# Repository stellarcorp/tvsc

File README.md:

#TVSC

This repository is the principal codebase for the Tennessee Valley Stellar Corporation. We are a community-scale space agency in east Tennessee dedicated to the open development of technologies enabling the public use of space.

## Repository structure

There are three main sections to the repository. The most active development at the moment is taking place in the [hal](./hal) and the [electronics](./electronics) directories. The hal directory contains the Hardware Abstraction Layer. The electronics directory holds our PCB design work. The rest of the repository (the third section) consists of older code that is in need of maintenance/documentation or deletion.

## Getting started

### Bazel

We use Bazel for our build system. It is one of the few build tools that allow for multi-language, cross-platform hermetic builds. For more information, checkout https://bazel.build/

Part of Bazel is a command line tool called [Bazelisk](https://github.com/bazelbuild/bazelisk). This tool manages Bazel installations on your local machine and allows us to specify *in the repo itself* the version of Bazel to use and prevents build errors due to build system versioning. Bazelisk executables are checked into the top-level of this repo. Please use them when building.

On the first run of bazelisk on a given computer, it will download the correct version of Bazel. So, this first build may take a while.

### Toolchain

The build uses the local toolchain for desktop builds. This toolchain should support C++20.

For embedded builds, the toolchain and system libraries are downloaded from various external repositories.

The builds are designed to work on Linux. Other systems can be added as needed.

### Do a test build for your local system:

From the top-level of the repo,
```
./bazelisk-linux-amd64 build --config=nucleo_l452re //...
```

The first build will take a long time, but future builds should be relatively fast.

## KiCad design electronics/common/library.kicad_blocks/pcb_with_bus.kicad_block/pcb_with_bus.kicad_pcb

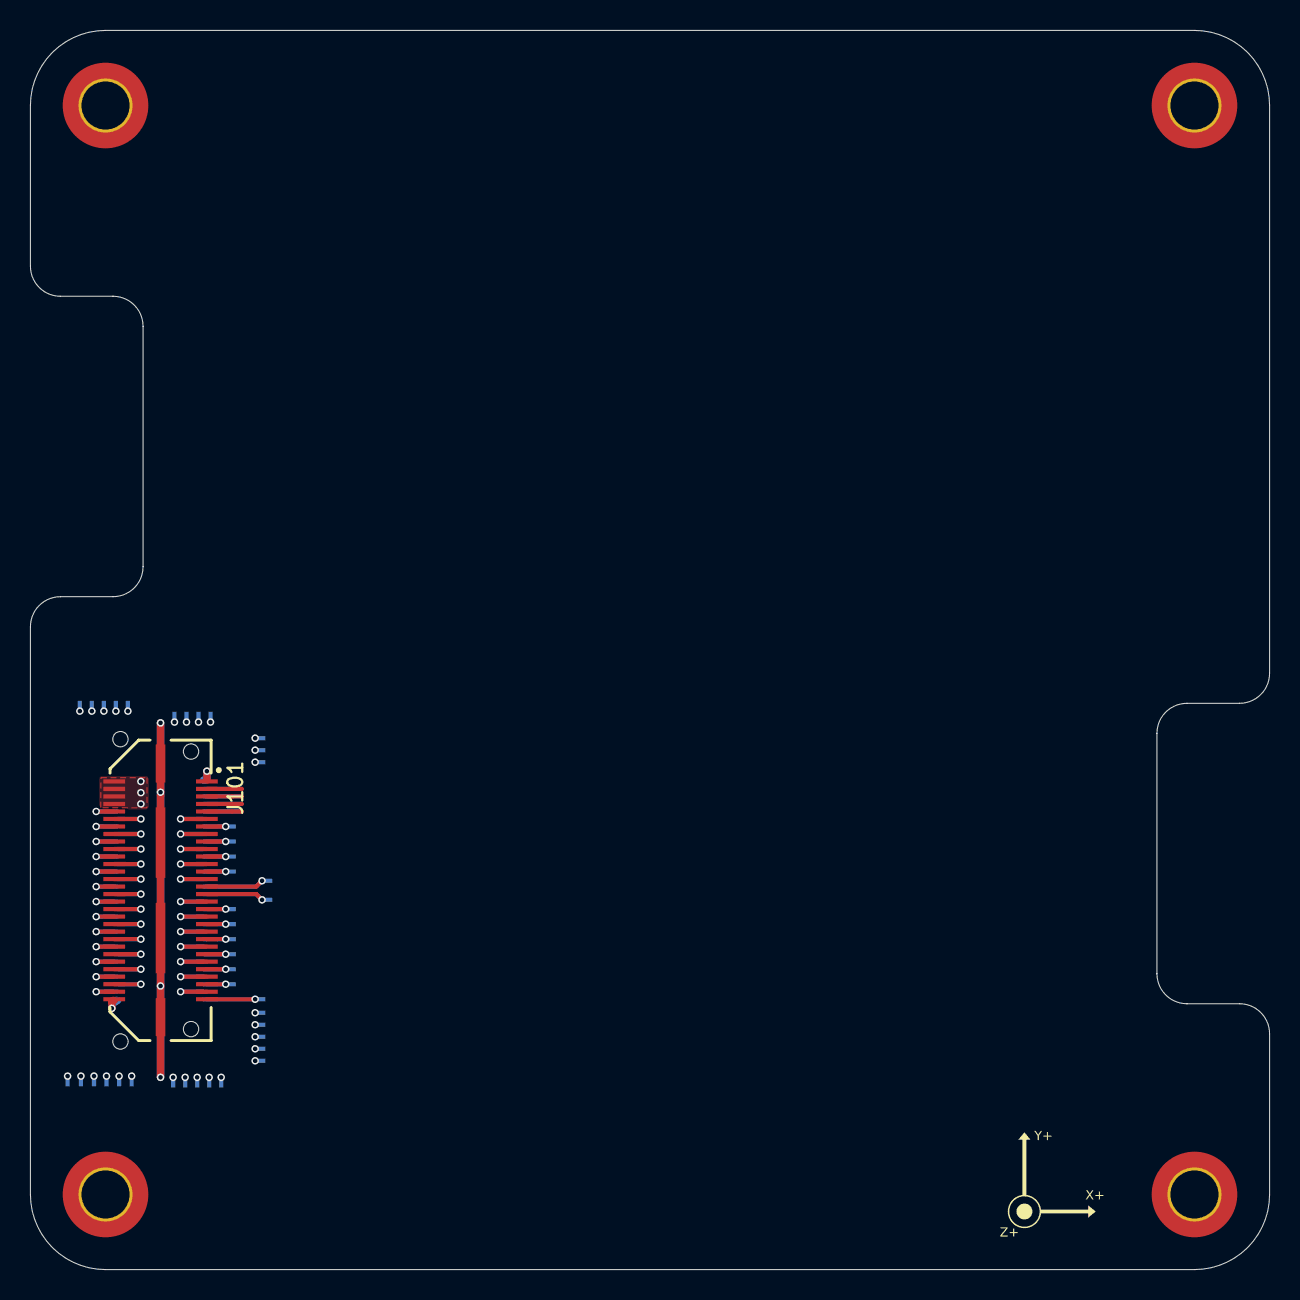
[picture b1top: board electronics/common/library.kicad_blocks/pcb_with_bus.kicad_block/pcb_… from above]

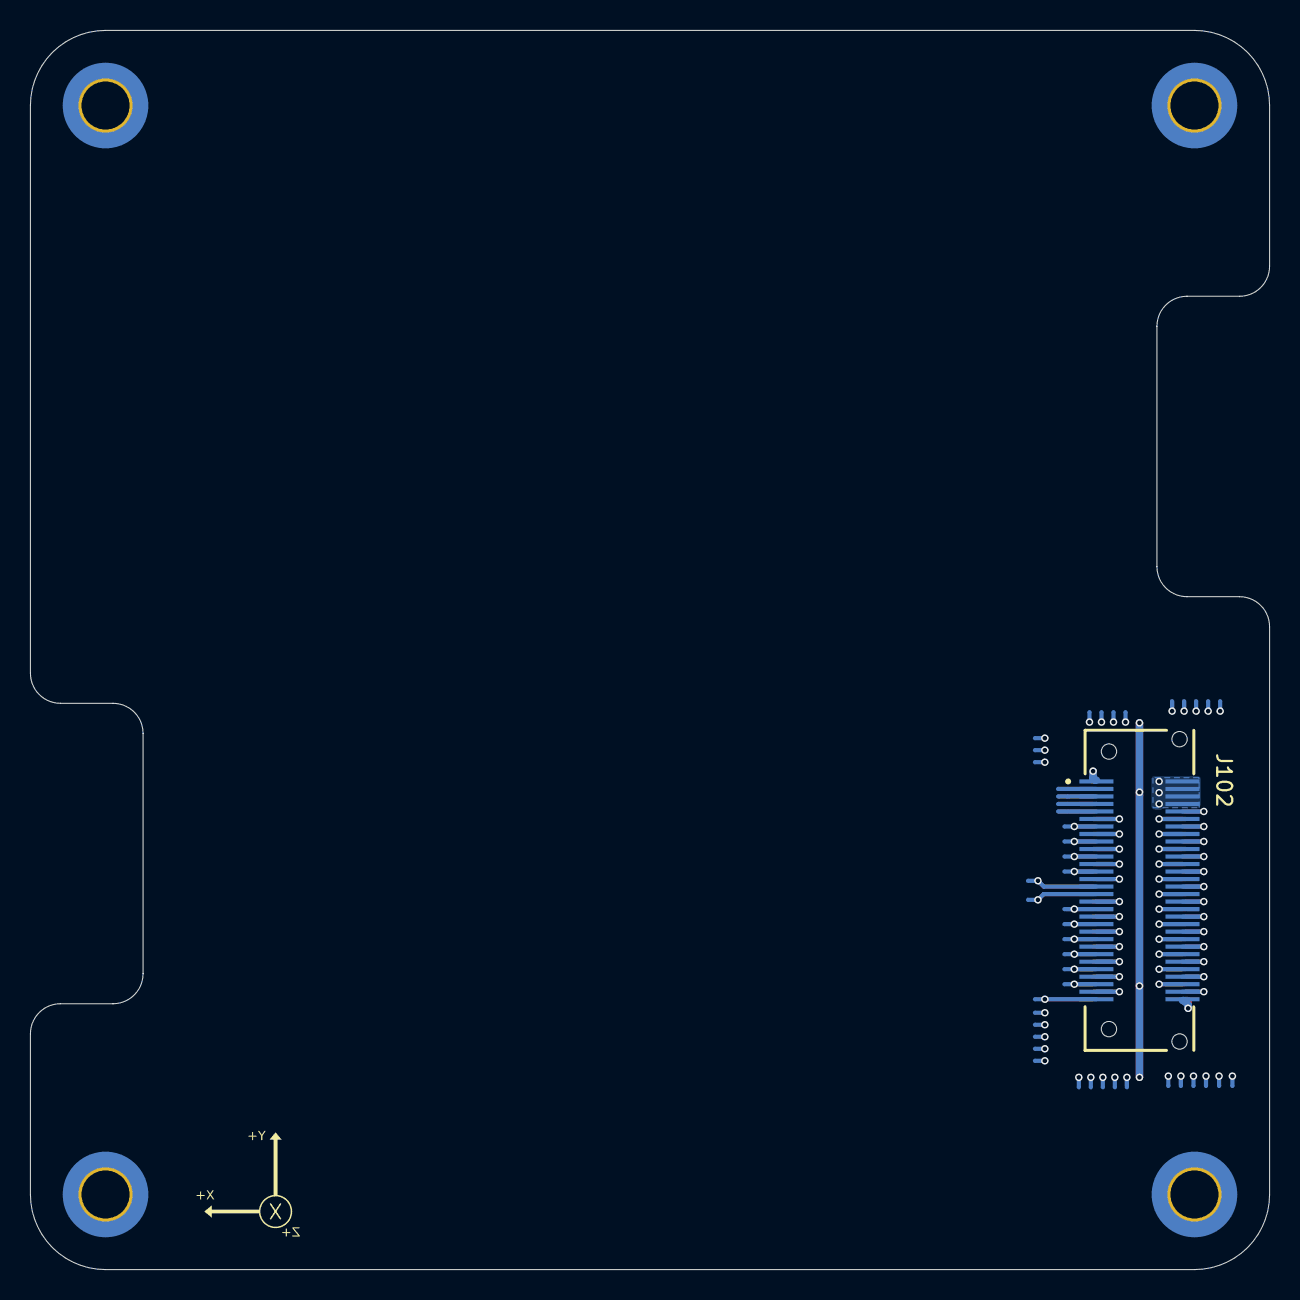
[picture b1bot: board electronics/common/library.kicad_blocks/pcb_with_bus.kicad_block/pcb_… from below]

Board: 4 copper layers, 82.5 x 82.5 mm, 52 parts (46 on the bottom side), 52 nets.

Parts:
J101: QTH-030-07-L-D-A; SAMTEC_QTH-030-07-L-D-A
J102: QSH-030-01-L-D-A; SAMTEC_QSH-030-01-L-D-A
NT101, NT102, NT103, NT104, NT105, NT106, NT107, NT108, NT109, NT110, NT111, NT112, NT113, NT114, NT115, NT116, NT117, NT118, NT119, NT120, NT121, NT122, NT123, NT124, NT125, NT126, NT127, NT128, NT129, NT130, NT131, NT132, NT133, NT134, NT135, NT136, NT137, NT138, NT139, NT140, NT141, NT142, NT143, NT144, NT145, NT146, NT147, NT148, NT149: NetTie_2; NetTie-2_SMD_Pad0.279mm
PCB101: Core_Board

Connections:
/PCB with bus/CANH_INTERNAL: J101.29, J102.29, NT136.1
/PCB with bus/CANL_INTERNAL: J101.31, J102.31, NT137.1
/PCB with bus/NRST_CTRL_INTERNAL: J102.07, NT134.1
/PCB with bus/NRST_INTERNAL: J101.07, NT130.1
/PCB with bus/SIGNAL_10_INTERNAL: J101.10, J102.10, NT101.2
/PCB with bus/SIGNAL_12_INTERNAL: J101.12, J102.12, NT102.2
/PCB with bus/SIGNAL_13_INTERNAL: J101.13, J102.13, NT121.1
/PCB with bus/SIGNAL_14_INTERNAL: J101.14, J102.14, NT103.2
/PCB with bus/SIGNAL_15_INTERNAL: J101.15, J102.15, NT122.1
/PCB with bus/SIGNAL_16_INTERNAL: J101.16, J102.16, NT104.2
/PCB with bus/SIGNAL_17_INTERNAL: J101.17, J102.17, NT123.1
/PCB with bus/SIGNAL_18_INTERNAL: J101.18, J102.18, NT105.2
/PCB with bus/SIGNAL_19_INTERNAL: J101.19, J102.19, NT124.1
/PCB with bus/SIGNAL_20_INTERNAL: J101.20, J102.20, NT106.2
/PCB with bus/SIGNAL_21_INTERNAL: J101.21, J102.21, NT125.1
/PCB with bus/SIGNAL_22_INTERNAL: J101.22, J102.22, NT107.2
/PCB with bus/SIGNAL_23_INTERNAL: J101.23, J102.23, NT126.1
/PCB with bus/SIGNAL_24_INTERNAL: J101.24, J102.24, NT108.2
/PCB with bus/SIGNAL_25_INTERNAL: J101.25, J102.25, NT127.1
/PCB with bus/SIGNAL_26_INTERNAL: J101.26, J102.26, NT109.2
/PCB with bus/SIGNAL_38_INTERNAL: J101.38, J102.38, NT110.2
/PCB with bus/SIGNAL_39_INTERNAL: J101.39, J102.39, NT138.1
/PCB with bus/SIGNAL_40_INTERNAL: J101.40, J102.40, NT111.2
/PCB with bus/SIGNAL_41_INTERNAL: J101.41, J102.41, NT139.1
/PCB with bus/SIGNAL_42_INTERNAL: J101.42, J102.42, NT112.2
/PCB with bus/SIGNAL_43_INTERNAL: J101.43, J102.43, NT140.1
/PCB with bus/SIGNAL_44_INTERNAL: J101.44, J102.44, NT113.2
/PCB with bus/SIGNAL_45_INTERNAL: J101.45, J102.45, NT141.1
/PCB with bus/SIGNAL_46_INTERNAL: J101.46, J102.46, NT114.2
/PCB with bus/SIGNAL_47_INTERNAL: J101.47, J102.47, NT142.1
/PCB with bus/SIGNAL_48_INTERNAL: J101.48, J102.48, NT115.2
/PCB with bus/SIGNAL_49_INTERNAL: J101.49, J102.49, NT143.1
/PCB with bus/SIGNAL_50_INTERNAL: J101.50, J102.50, NT116.2
/PCB with bus/SIGNAL_51_INTERNAL: J101.51, J102.51, NT144.1
/PCB with bus/SIGNAL_52_INTERNAL: J101.52, J102.52, NT117.2
/PCB with bus/SIGNAL_53_INTERNAL: J101.53, J102.53, NT145.1
/PCB with bus/SIGNAL_54_INTERNAL: J101.54, J102.54, NT118.2
/PCB with bus/SIGNAL_55_INTERNAL: J101.55, J102.55, NT146.1
/PCB with bus/SIGNAL_56_INTERNAL: J101.56, J102.56, NT119.2
/PCB with bus/SIGNAL_57_INTERNAL: J101.57, J102.57, NT147.1
/PCB with bus/SIGNAL_58_INTERNAL: J101.58, J102.58, NT120.2
/PCB with bus/SIGNAL_59_INTERNAL: J101.59, J102.59, NT148.1
/PCB with bus/SWCLK_CTRL_INTERNAL: J102.03, NT132.1
/PCB with bus/SWCLK_INTERNAL: J101.03, NT128.1
/PCB with bus/SWDIO_CTRL_INTERNAL: J102.05, NT133.1
/PCB with bus/SWDIO_INTERNAL: J101.05, NT129.1
/PCB with bus/SWO_CTRL_INTERNAL: J102.09, NT135.1
/PCB with bus/SWO_INTERNAL: J101.09, NT131.1
/PCB with bus/VBUS: J101.27, J101.28, J101.30, J101.32, J101.33, J101.34, J102.27, J102.28, J102.30, J102.32, J102.33, J102.34
/PCB with bus/VSOLAR: J101.02, J101.04, J101.06, J101.08, J102.02, J102.04, J102.06, J102.08
/PCB with bus/WAKE_INTERNAL: J101.35, J102.35, NT149.1
GND: J101.01, J101.11, J101.36, J101.37, J101.60, J101.G1 (GND), J101.G2 (GND__1), J101.G3 (GND__2), J101.G4 (GND__3), J102.01, J102.11, J102.36, J102.37, J102.60, J102.S1 (GND), J102.S2 (GND__1), J102.S3 (GND__2), J102.S4 (GND__3), PCB101.MH1, PCB101.MH2, PCB101.MH3, PCB101.MH4

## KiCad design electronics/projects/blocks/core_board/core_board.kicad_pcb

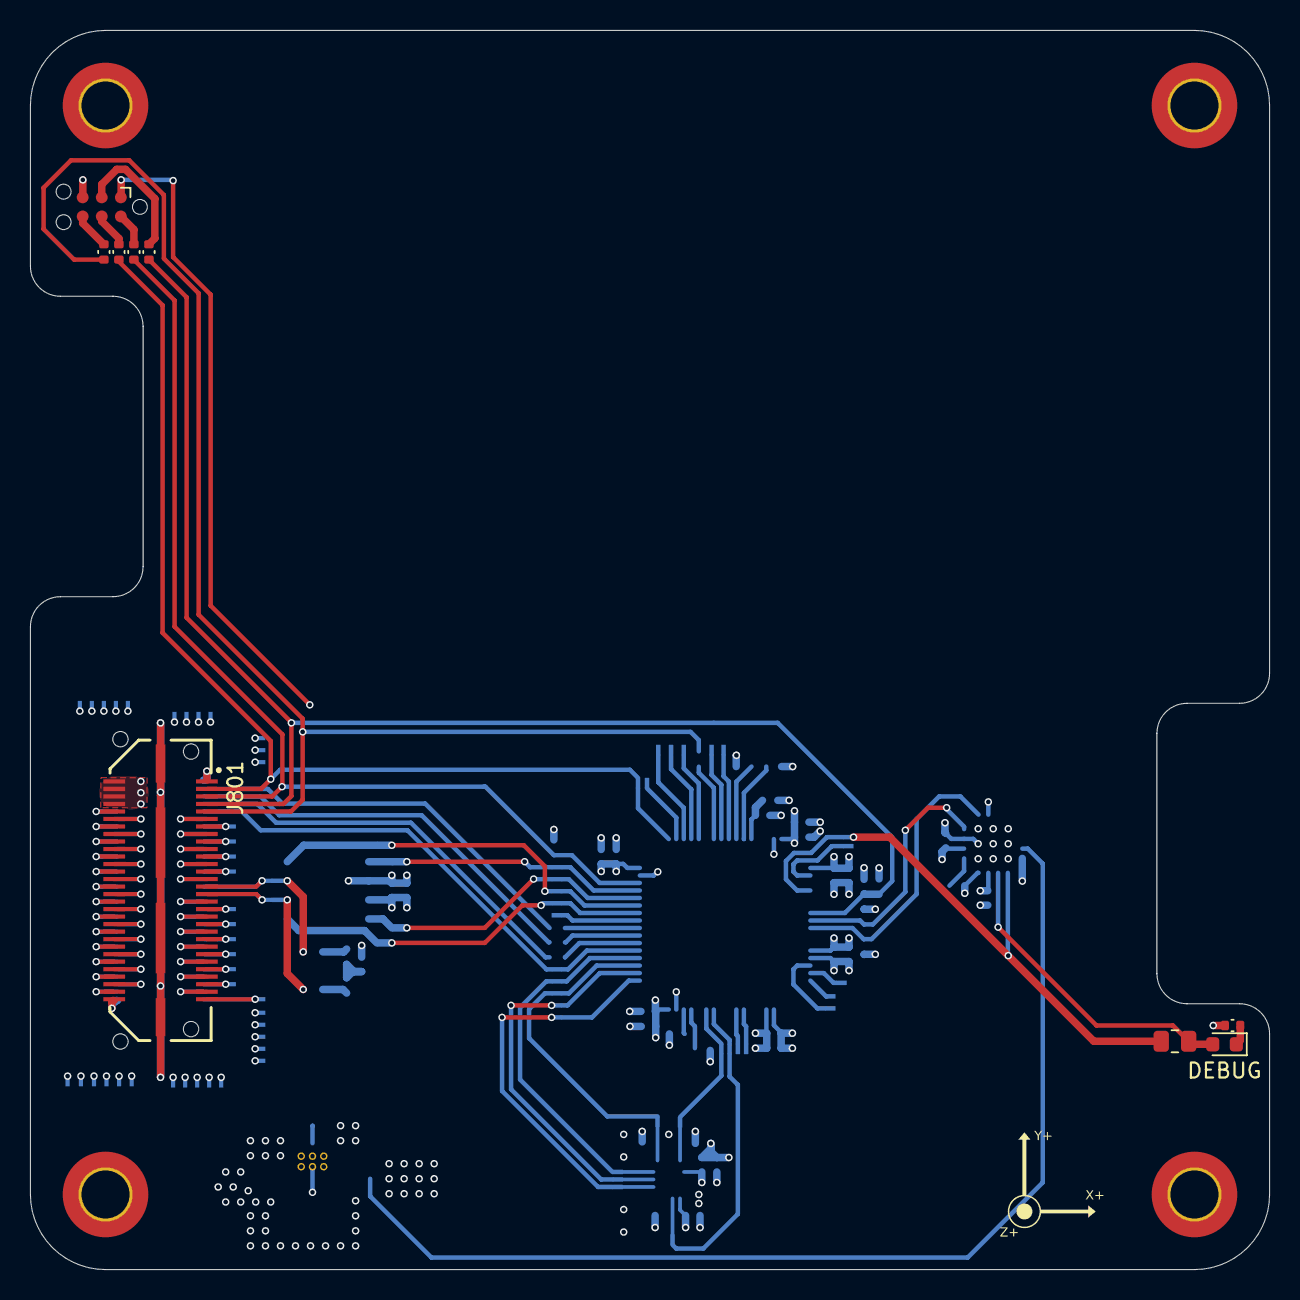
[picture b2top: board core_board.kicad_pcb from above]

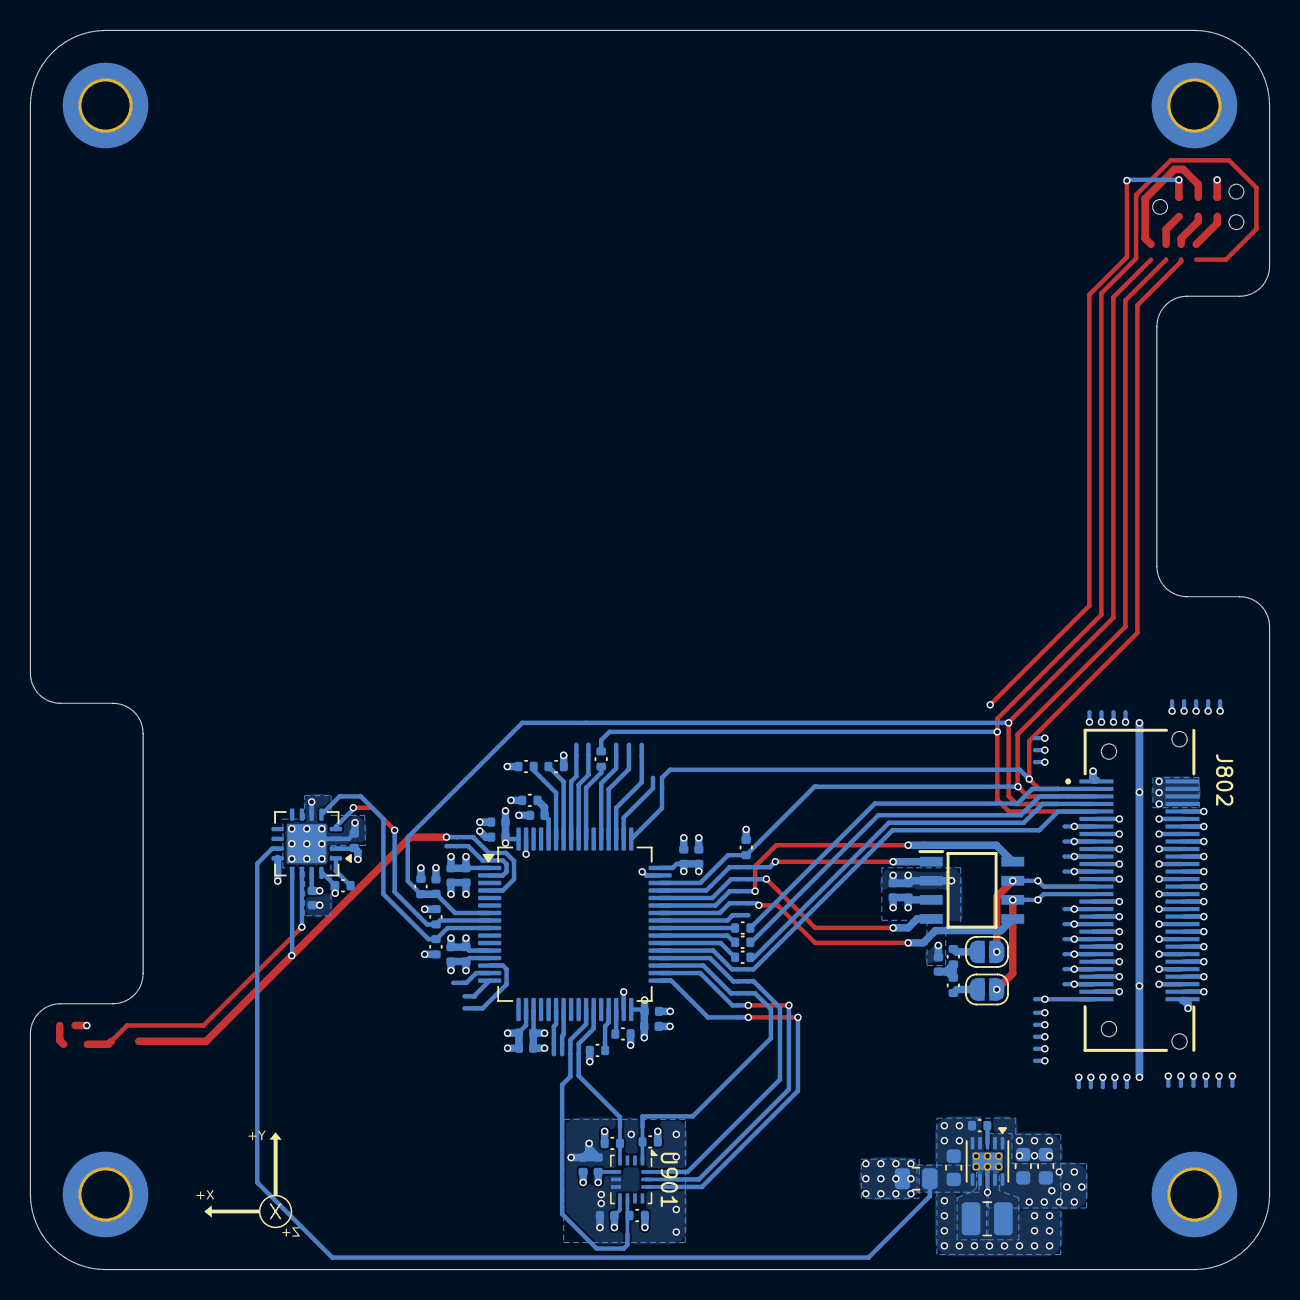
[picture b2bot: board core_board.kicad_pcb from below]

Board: 4 copper layers, 82.5 x 82.5 mm, 150 parts (136 on the bottom side), 135 nets.

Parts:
C301, C302, C305, C306, C308, C309, C311, C312, C402, C403, C501, C502, C902, C903: 100n; Nondescript_C_0402_1005Metric
C303, C304, C307, C310, C313, C314, C401, C901: 1u; Nondescript_C_0402_1005Metric
C601, C603: 22u; Nondescript_C_0603_1608Metric
C602: 10u; Nondescript_C_0603_1608Metric
D101: DEBUG; LED_0603_1608Metric
J701: STLINK; Tag-Connect_TC2030-IDC-NL_2x03_P1.27mm_Vertical
J801: QTH-030-07-L-D-A; SAMTEC_QTH-030-07-L-D-A
J802: QSH-030-01-L-D-A; SAMTEC_QSH-030-01-L-D-A
JP401, JP402: SolderJumper_2_Open; SolderJumper-2_P1.3mm_Open_RoundedPad1.0x1.5mm
L601: 2.2µH; L_1008_2520Metric
NT301, NT302, NT303, NT304, NT305, NT306, NT307, NT308, NT309, NT310, NT311, NT312, NT313, NT314, NT315, NT316, NT317, NT318, NT319, NT320, NT321, NT322, NT323, NT324, NT325, NT326, NT901, NT902, NT903, NT904, NT905, NT906: NetTie_2; NetTie-2_SMD_Pad0.3mm
NT401, NT402, NT403, NT404: NetTie_2; NetTie-2_SMD_Pad0.5mm
NT801, NT802, NT803, NT804, NT805, NT806, NT807, NT808, NT809, NT810, NT811, NT812, NT813, NT814, NT815, NT816, NT817, NT818, NT819, NT820, NT821, NT822, NT823, NT824, NT825, NT826, NT827, NT828, NT829, NT830, NT831, NT832, NT833, NT834, NT835, NT836, NT837, NT838, NT839, NT840, NT841, NT842, NT843, NT844, NT845, NT846, NT847, NT848, NT849: NetTie_2; NetTie-2_SMD_Pad0.279mm
PCB801: Core_Board
R101, R602: 100m; R_0805_2012Metric
R102, R302, R303, R304, R313, R701, R702, R703, R704: 33; Nondescript_R_0402_1005Metric
R301, R305, R306, R307, R308, R309, R310, R311, R312, R501, R901, R902, R903: 9k31; Nondescript_R_0402_1005Metric
R401, R402: 60; Nondescript_R_0402_1005Metric
R601: 36k5; Nondescript_R_0402_1005Metric
U301: STM32L452RCTx; LQFP-64_10x10mm_P0.5mm
U401: TCAN330DR; SOIC127P600X175-8N
U501: PAC1934T-I/JQ; UQFN-16-1EP_4x4mm_P0.65mm_EP2.6x2.6mm
U601: TPS63900; WSON-10-1EP_2.5x2.5mm_P0.5mm_EP1.2x2mm_ThermalVias
U901: BMI323; Bosch_LGA-14_3x2.5mm_P0.5mm

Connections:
/core_board/3V3: C303.1, C304.1, C305.1, C306.1, C307.1, C308.1, C309.1, C310.1, C311.1, C312.1, C313.1, C314.1, C401.1, C402.1, C501.1, C502.1, C901.1, C902.1, C903.1, J701.1 (T_VCC), R301.1, R305.1, R307.1, R308.1, R309.1, R310.1, R311.1, R312.1, R501.1, R602.2, R901.1, R902.1, R903.1, U301.1 (VBAT), U301.13 (VDDA), U301.19 (VDD), U301.32 (VDD), U301.48 (VDDUSB), U301.64 (VDD), U401.3 (VCC), U501.2 (V_{DD}), U501.12 (SENSE1-), U501.15 (V_{DD}IO), U501.16 (~PWRDN), U901.5 (VDDIO), U901.8 (VDD)
/core_board/CAN.H: JP401.1 (A), NT832.2, U401.7 (CANH)
/core_board/CAN.L: JP402.2 (B), NT833.2, U401.6 (CANL)
/core_board/DEBUG_LED_N: D101.2 (A), R101.2, U501.14 (SENSE2-)
/core_board/DEBUG_LED_P: NT305.1, R101.1, U501.13 (SENSE2+)
/core_board/I2C1.SCL: R308.2, U301.58 (PB6)
/core_board/I2C1.SDA: R311.2, U301.59 (PB7)
/core_board/I2C2.SCL: R309.2, U301.29 (PB10)
/core_board/I2C2.SDA: R312.2, U301.30 (PB11)
/core_board/I2C3.SCL: R301.2, U301.8 (PC0), U501.4 (SCL)
/core_board/I2C3.SDA: R307.2, U301.9 (PC1), U501.5 (SDA)
/core_board/IMU1_INT_1: NT313.2, NT905.2
/core_board/IMU1_INT_2: NT312.2, NT906.2
/core_board/Isolated Bus/pcb_with_bus/CANH_INTERNAL: J801.29, J802.29, NT832.1
/core_board/Isolated Bus/pcb_with_bus/CANL_INTERNAL: J801.31, J802.31, NT833.1
/core_board/Isolated Bus/pcb_with_bus/NRST_CTRL_INTERNAL: J802.07, NT848.1
/core_board/Isolated Bus/pcb_with_bus/NRST_INTERNAL: J801.07, NT823.1
/core_board/Isolated Bus/pcb_with_bus/SIGNAL_10_INTERNAL: J801.10, J802.10, NT801.2
/core_board/Isolated Bus/pcb_with_bus/SIGNAL_12_INTERNAL: J801.12, J802.12, NT802.2
/core_board/Isolated Bus/pcb_with_bus/SIGNAL_13_INTERNAL: J801.13, J802.13, NT825.1
/core_board/Isolated Bus/pcb_with_bus/SIGNAL_14_INTERNAL: J801.14, J802.14, NT803.2
/core_board/Isolated Bus/pcb_with_bus/SIGNAL_15_INTERNAL: J801.15, J802.15, NT826.1
/core_board/Isolated Bus/pcb_with_bus/SIGNAL_16_INTERNAL: J801.16, J802.16, NT804.2
/core_board/Isolated Bus/pcb_with_bus/SIGNAL_17_INTERNAL: J801.17, J802.17, NT827.1
/core_board/Isolated Bus/pcb_with_bus/SIGNAL_18_INTERNAL: J801.18, J802.18, NT805.2
/core_board/Isolated Bus/pcb_with_bus/SIGNAL_19_INTERNAL: J801.19, J802.19, NT828.1
/core_board/Isolated Bus/pcb_with_bus/SIGNAL_20_INTERNAL: J801.20, J802.20, NT806.2
/core_board/Isolated Bus/pcb_with_bus/SIGNAL_21_INTERNAL: J801.21, J802.21, NT829.1
/core_board/Isolated Bus/pcb_with_bus/SIGNAL_22_INTERNAL: J801.22, J802.22, NT807.2
/core_board/Isolated Bus/pcb_with_bus/SIGNAL_23_INTERNAL: J801.23, J802.23, NT830.1
/core_board/Isolated Bus/pcb_with_bus/SIGNAL_24_INTERNAL: J801.24, J802.24, NT808.2
/core_board/Isolated Bus/pcb_with_bus/SIGNAL_25_INTERNAL: J801.25, J802.25, NT831.1
/core_board/Isolated Bus/pcb_with_bus/SIGNAL_26_INTERNAL: J801.26, J802.26, NT809.2
/core_board/Isolated Bus/pcb_with_bus/SIGNAL_35_INTERNAL: J801.35, J802.35, NT834.1
/core_board/Isolated Bus/pcb_with_bus/SIGNAL_38_INTERNAL: J801.38, J802.38, NT810.2
/core_board/Isolated Bus/pcb_with_bus/SIGNAL_39_INTERNAL: J801.39, J802.39, NT835.1
/core_board/Isolated Bus/pcb_with_bus/SIGNAL_40_INTERNAL: J801.40, J802.40, NT811.2
/core_board/Isolated Bus/pcb_with_bus/SIGNAL_41_INTERNAL: J801.41, J802.41, NT836.1
/core_board/Isolated Bus/pcb_with_bus/SIGNAL_42_INTERNAL: J801.42, J802.42, NT812.2
/core_board/Isolated Bus/pcb_with_bus/SIGNAL_43_INTERNAL: J801.43, J802.43, NT837.1
/core_board/Isolated Bus/pcb_with_bus/SIGNAL_44_INTERNAL: J801.44, J802.44, NT813.2
/core_board/Isolated Bus/pcb_with_bus/SIGNAL_45_INTERNAL: J801.45, J802.45, NT838.1
/core_board/Isolated Bus/pcb_with_bus/SIGNAL_46_INTERNAL: J801.46, J802.46, NT814.2
/core_board/Isolated Bus/pcb_with_bus/SIGNAL_47_INTERNAL: J801.47, J802.47, NT839.1
/core_board/Isolated Bus/pcb_with_bus/SIGNAL_48_INTERNAL: J801.48, J802.48, NT815.2
/core_board/Isolated Bus/pcb_with_bus/SIGNAL_49_INTERNAL: J801.49, J802.49, NT840.1
/core_board/Isolated Bus/pcb_with_bus/SIGNAL_50_INTERNAL: J801.50, J802.50, NT816.2
/core_board/Isolated Bus/pcb_with_bus/SIGNAL_51_INTERNAL: J801.51, J802.51, NT841.1
/core_board/Isolated Bus/pcb_with_bus/SIGNAL_52_INTERNAL: J801.52, J802.52, NT817.2
/core_board/Isolated Bus/pcb_with_bus/SIGNAL_53_INTERNAL: J801.53, J802.53, NT842.1
/core_board/Isolated Bus/pcb_with_bus/SIGNAL_54_INTERNAL: J801.54, J802.54, NT818.2
/core_board/Isolated Bus/pcb_with_bus/SIGNAL_55_INTERNAL: J801.55, J802.55, NT843.1
/core_board/Isolated Bus/pcb_with_bus/SIGNAL_56_INTERNAL: J801.56, J802.56, NT819.2
/core_board/Isolated Bus/pcb_with_bus/SIGNAL_57_INTERNAL: J801.57, J802.57, NT844.1
/core_board/Isolated Bus/pcb_with_bus/SIGNAL_58_INTERNAL: J801.58, J802.58, NT820.2
/core_board/Isolated Bus/pcb_with_bus/SIGNAL_59_INTERNAL: J801.59, J802.59, NT845.1
/core_board/Isolated Bus/pcb_with_bus/SWCLK_CTRL_INTERNAL: J802.03, NT846.1
/core_board/Isolated Bus/pcb_with_bus/SWCLK_INTERNAL: J801.03, NT821.1
/core_board/Isolated Bus/pcb_with_bus/SWDIO_CTRL_INTERNAL: J802.05, NT847.1
/core_board/Isolated Bus/pcb_with_bus/SWDIO_INTERNAL: J801.05, NT822.1
/core_board/Isolated Bus/pcb_with_bus/SWO_CTRL_INTERNAL: J802.09, NT849.1
/core_board/Isolated Bus/pcb_with_bus/SWO_INTERNAL: J801.09, NT824.1
/core_board/SPI2.CS: NT323.2, NT901.1
/core_board/SPI2.MISO: NT325.2, NT904.1
/core_board/SPI2.MOSI: NT326.2, NT903.1
/core_board/SPI2.SCK: NT324.2, NT902.1
/core_board/SWD.NRST: C302.1, NT823.2, R305.2, R702.1, U301.7 (NRST)
/core_board/SWD.SWCLK: NT318.2, NT821.2, R703.1
/core_board/SWD.SWDIO: NT822.2, R310.2, R701.1, U301.46 (PA13)
/core_board/SWD.SWO: NT824.2, R313.2, R704.1
/core_board/SWD_CTRL.NRST: NT848.2, R302.2
/core_board/SWD_CTRL.SWCLK: NT846.2, R304.2
/core_board/SWD_CTRL.SWDIO: NT847.2, R303.2
/core_board/SWD_CTRL.SWO: NT301.1, NT849.2
/core_board/VBUS: C601.1, C602.1, J801.27, J801.28, J801.30, J801.32, J801.33, J801.34, J802.27, J802.28, J802.30, J802.32, J802.33, J802.34, U601.1 (EN), U601.2 (SEL), U601.10 (VIN)
/core_board/VSOLAR: J801.02, J801.04, J801.06, J801.08, J802.02, J802.04, J802.06, J802.08
/core_board/can_bus/CANH_TERMINATION: JP401.2 (B), R401.1
/core_board/can_bus/CANL_TERMINATION: JP402.1 (A), R402.2
/core_board/can_bus/CAN_RX: NT310.2, NT403.1
/core_board/can_bus/CAN_SHUTDOWN: NT308.2, NT404.1
/core_board/can_bus/CAN_SILENT: NT309.2, NT401.1
/core_board/can_bus/CAN_TX: NT311.2, NT402.1
/core_board/mcu/BOARD_ID_PWR_INTERNAL: NT316.1, U301.22 (PA6)
/core_board/mcu/BOARD_ID_SENS_INTERNAL: NT317.1, U301.23 (PA7)
/core_board/mcu/BOARD_ID_VERSION_INTERNAL: NT315.1, U301.16 (PA2)
/core_board/mcu/BOOT0: C301.1, R306.1, U301.60 (PH3)
/core_board/mcu/CAN1_RX_INTERNAL: NT310.1, U301.44 (PA11)
/core_board/mcu/CAN1_SHUTDOWN_INTERNAL: NT308.1, U301.42 (PA9)
/core_board/mcu/CAN1_SILENT_INTERNAL: NT309.1, U301.43 (PA10)
/core_board/mcu/CAN1_TX_INTERNAL: NT311.1, U301.45 (PA12)
/core_board/mcu/DEBUG_LED_INTERNAL: NT305.2, U301.4 (PC15)
/core_board/mcu/NRST_CTRL_INTERNAL: R302.1, U301.38 (PC7)
/core_board/mcu/PERIPH_INT_1_INTERNAL: NT307.1, U301.14 (PA0)
/core_board/mcu/PERIPH_INT_2_INTERNAL: NT306.2, U301.2 (PC13)
/core_board/mcu/PERIPH_INT_3_INTERNAL: NT314.1, U301.41 (PA8)
/core_board/mcu/PERIPH_INT_4_INTERNAL: NT312.1, U301.26 (PB0)
/core_board/mcu/PERIPH_INT_5_INTERNAL: NT313.1, U301.27 (PB1)
/core_board/mcu/SPI1_MISO_INTERNAL: NT321.1, U301.56 (PB4)
/core_board/mcu/SPI1_MOSI_INTERNAL: NT322.1, U301.57 (PB5)
/core_board/mcu/SPI1_SCK_INTERNAL: NT319.1, U301.15 (PA1)
/core_board/mcu/SPI1_SPI3_CS_INTERNAL: NT320.1, U301.50 (PA15)
/core_board/mcu/SPI2_CS_INTERNAL: NT323.1, U301.33 (PB12)
/core_board/mcu/SPI2_MISO_INTERNAL: NT325.1, U301.35 (PB14)
/core_board/mcu/SPI2_MOSI_INTERNAL: NT326.1, U301.36 (PB15)
/core_board/mcu/SPI2_SCK_INTERNAL: NT324.1, U301.34 (PB13)
/core_board/mcu/SPI3_MISO_INTERNAL: NT303.2, U301.52 (PC11)
/core_board/mcu/SPI3_MOSI_INTERNAL: NT304.2, U301.53 (PC12)
/core_board/mcu/SPI3_SCK_INTERNAL: NT302.2, U301.51 (PC10)
/core_board/mcu/SWCLK_CTRL_INTERNAL: R304.1, U301.40 (PC9)
/core_board/mcu/SWCLK_INTERNAL: NT318.1, U301.49 (PA14)
/core_board/mcu/SWDIO_CTRL_INTERNAL: R303.1, U301.39 (PC8)
/core_board/mcu/SWO_CTRL_INTERNAL: NT301.2, U301.37 (PC6)
/core_board/power_measurement/BOARD_LOAD_+: C603.1, R602.1, U501.11 (SENSE1+), U601.6 (VOUT)
GND: C301.2, C302.2, C303.2, C304.2, C305.2, C306.2, C307.2, C308.2, C309.2, C310.2, C311.2, C312.2, C313.2, C314.2, C401.2, C402.2, C403.1, C501.2, C502.2, C601.2, C602.2, C603.2, C901.2, C902.2, C903.2, J701.5 (GND), J801.01, J801.11, J801.36, J801.37, J801.60, J801.G1 (GND), J801.G2 (GND__1), J801.G3 (GND__2), J801.G4 (GND__3), J802.01, J802.11, J802.36, J802.37, J802.60, J802.S1 (GND), J802.S2 (GND__1), J802.S3 (GND__2), J802.S4 (GND__3), PCB801.MH1, PCB801.MH2, PCB801.MH3, PCB801.MH4, R102.2, R306.2, R601.2, U301.12 (VSSA), U301.18 (VSS), U301.31 (VSS), U301.47 (VSS), U301.63 (VSS), U401.2 (GND), U501.3 (GND), U501.6 (ADDRSEL), U501.17 (EP), U601.4 (CFG2), U601.5 (CFG3), U601.8 (GND), U601.11 (GND), U901.6 (GNDIO), U901.7 (GND)
unnamed: C403.2, R401.2, R402.1
unnamed: D101.1 (K), R102.1
unnamed: J701.3 (T_NRST), R702.2
unnamed: J701.4 (T_SWCLK), R703.2
unnamed: J701.2 (T_SWDIO), R701.2
unnamed: J701.6 (T_SWO), R704.2
unnamed: R313.1, U301.55 (PB3)
unnamed: NT403.2, U401.4 (RXD)
unnamed: NT401.2, U401.8 (S)
unnamed: NT404.2, U401.5 (SHDN)
unnamed: NT402.2, U401.1 (TXD)
unnamed: R501.2, U501.1 (SLOW)
unnamed: R601.1, U601.3 (CFG1)
unnamed: L601.2, U601.9 (LX1)
unnamed: L601.1, U601.7 (LX2)
unnamed: NT901.2, U901.12 (CSB)
unnamed: NT905.1, R903.2, U901.4 (INT1)
unnamed: NT906.1, R902.2, U901.9 (INT2)
unnamed: NT902.2, U901.13 (SCx)
unnamed: NT904.2, R901.2, U901.1 (SDO)
unnamed: NT903.2, U901.14 (SDx)

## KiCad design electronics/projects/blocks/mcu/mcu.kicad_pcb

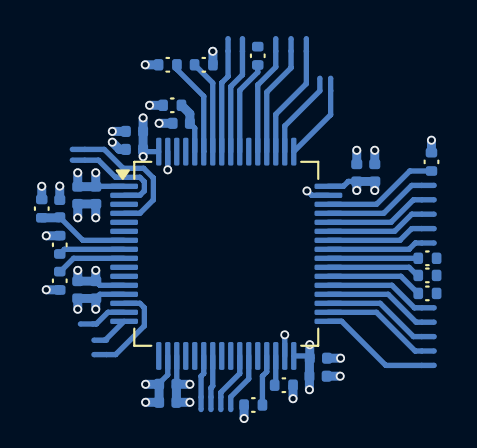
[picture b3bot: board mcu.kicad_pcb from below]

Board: 4 copper layers, 54 parts (54 on the bottom side), 41 nets.

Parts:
C101, C102, C105, C106, C108, C109, C111, C112: 100n; Nondescript_C_0402_1005Metric
C103, C104, C107, C110, C113, C114: 1u; Nondescript_C_0402_1005Metric
NT101, NT102, NT103, NT104, NT105, NT106, NT107, NT108, NT109, NT110, NT111, NT112, NT113, NT114, NT115, NT116, NT117, NT118, NT119, NT120, NT121, NT122, NT123, NT124, NT125, NT126: NetTie_2; NetTie-2_SMD_Pad0.3mm
R101, R105, R106, R107, R108, R109, R110, R111, R112: 9k31; Nondescript_R_0402_1005Metric
R102, R103, R104, R113: 33; Nondescript_R_0402_1005Metric
U101: STM32L452RCTx; LQFP-64_10x10mm_P0.5mm

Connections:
/mcu/3V3: C103.1, C104.1, C105.1, C106.1, C107.1, C108.1, C109.1, C110.1, C111.1, C112.1, C113.1, C114.1, R101.1, R105.1, R107.1, R108.1, R109.1, R110.1, R111.1, R112.1, U101.1 (VBAT), U101.13 (VDDA), U101.19 (VDD), U101.32 (VDD), U101.48 (VDDUSB), U101.64 (VDD)
/mcu/BOARD_ID_PWR_INTERNAL: NT116.1, U101.22 (PA6)
/mcu/BOARD_ID_SENS_INTERNAL: NT117.1, U101.23 (PA7)
/mcu/BOARD_ID_VERSION_INTERNAL: NT115.1, U101.16 (PA2)
/mcu/BOOT0: C101.1, R106.1, U101.60 (PH3)
/mcu/CAN1_RX_INTERNAL: NT110.1, U101.44 (PA11)
/mcu/CAN1_SHUTDOWN_INTERNAL: NT108.1, U101.42 (PA9)
/mcu/CAN1_SILENT_INTERNAL: NT109.1, U101.43 (PA10)
/mcu/CAN1_TX_INTERNAL: NT111.1, U101.45 (PA12)
/mcu/DEBUG_LED_INTERNAL: NT105.2, U101.4 (PC15)
/mcu/I2C1_SCL: R108.2, U101.58 (PB6)
/mcu/I2C1_SDA: R111.2, U101.59 (PB7)
/mcu/I2C2_SCL: R109.2, U101.29 (PB10)
/mcu/I2C2_SDA: R112.2, U101.30 (PB11)
/mcu/I2C3_SCL: R101.2, U101.8 (PC0)
/mcu/I2C3_SDA: R107.2, U101.9 (PC1)
/mcu/NRST: C102.1, R105.2, U101.7 (NRST)
/mcu/NRST_CTRL_INTERNAL: R102.1, U101.38 (PC7)
/mcu/PERIPH_INT_1_INTERNAL: NT107.1, U101.14 (PA0)
/mcu/PERIPH_INT_2_INTERNAL: NT106.2, U101.2 (PC13)
/mcu/PERIPH_INT_3_INTERNAL: NT114.1, U101.41 (PA8)
/mcu/PERIPH_INT_4_INTERNAL: NT112.1, U101.26 (PB0)
/mcu/PERIPH_INT_5_INTERNAL: NT113.1, U101.27 (PB1)
/mcu/SPI1_MISO_INTERNAL: NT121.1, U101.56 (PB4)
/mcu/SPI1_MOSI_INTERNAL: NT122.1, U101.57 (PB5)
/mcu/SPI1_SCK_INTERNAL: NT119.1, U101.15 (PA1)
/mcu/SPI1_SPI3_CS_INTERNAL: NT120.1, U101.50 (PA15)
/mcu/SPI2_CS_INTERNAL: NT123.1, U101.33 (PB12)
/mcu/SPI2_MISO_INTERNAL: NT125.1, U101.35 (PB14)
/mcu/SPI2_MOSI_INTERNAL: NT126.1, U101.36 (PB15)
/mcu/SPI2_SCK_INTERNAL: NT124.1, U101.34 (PB13)
/mcu/SPI3_MISO_INTERNAL: NT103.2, U101.52 (PC11)
/mcu/SPI3_MOSI_INTERNAL: NT104.2, U101.53 (PC12)
/mcu/SPI3_SCK_INTERNAL: NT102.2, U101.51 (PC10)
/mcu/SWCLK_CTRL_INTERNAL: R104.1, U101.40 (PC9)
/mcu/SWCLK_INTERNAL: NT118.1, U101.49 (PA14)
/mcu/SWDIO: R110.2, U101.46 (PA13)
/mcu/SWDIO_CTRL_INTERNAL: R103.1, U101.39 (PC8)
/mcu/SWO_CTRL_INTERNAL: NT101.2, U101.37 (PC6)
GND: C101.2, C102.2, C103.2, C104.2, C105.2, C106.2, C107.2, C108.2, C109.2, C110.2, C111.2, C112.2, C113.2, C114.2, R106.2, U101.12 (VSSA), U101.18 (VSS), U101.31 (VSS), U101.47 (VSS), U101.63 (VSS)
unnamed: R113.1, U101.55 (PB3)

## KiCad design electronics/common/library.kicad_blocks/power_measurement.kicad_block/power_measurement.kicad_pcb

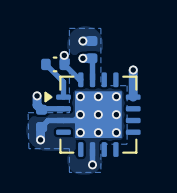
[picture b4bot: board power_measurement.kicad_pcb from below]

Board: 4 copper layers, 4 parts (4 on the bottom side), 3 nets.

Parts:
C101, C102: 100n; Nondescript_C_0402_1005Metric
R101: 9k31; Nondescript_R_0402_1005Metric
U101: PAC1934T-I/JQ; UQFN-16-1EP_4x4mm_P0.65mm_EP2.6x2.6mm

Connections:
/power_measurement/3V3: C101.1, C102.1, R101.1, U101.2 (V_{DD}), U101.12 (SENSE1-), U101.15 (V_{DD}IO), U101.16 (~PWRDN)
GND: C101.2, C102.2, U101.3 (GND), U101.6 (ADDRSEL), U101.17 (EP)
unnamed: R101.2, U101.1 (SLOW)

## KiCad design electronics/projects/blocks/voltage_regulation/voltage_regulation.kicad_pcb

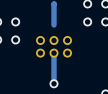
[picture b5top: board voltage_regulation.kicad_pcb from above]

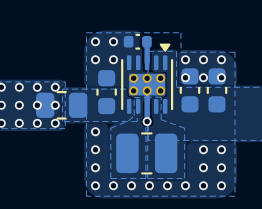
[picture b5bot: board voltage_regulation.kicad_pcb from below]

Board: 4 copper layers, 7 parts (7 on the bottom side), 6 nets.

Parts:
C101, C103: 22u; Nondescript_C_0603_1608Metric
C102: 10u; Nondescript_C_0603_1608Metric
L101: 2.2µH; L_1008_2520Metric
R101: 36k5; Nondescript_R_0402_1005Metric
R102: 100m; R_0805_2012Metric
U101: TPS63900; WSON-10-1EP_2.5x2.5mm_P0.5mm_EP1.2x2mm_ThermalVias

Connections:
/Voltage Regulation/BOARD_LOAD_+: C103.1, R102.1, U101.6 (VOUT)
/Voltage Regulation/VBUS: C101.1, C102.1, U101.1 (EN), U101.2 (SEL), U101.10 (VIN)
GND: C101.2, C102.2, C103.2, R101.2, U101.4 (CFG2), U101.5 (CFG3), U101.8 (GND), U101.11 (GND)
unnamed: R101.1, U101.3 (CFG1)
unnamed: L101.2, U101.9 (LX1)
unnamed: L101.1, U101.7 (LX2)

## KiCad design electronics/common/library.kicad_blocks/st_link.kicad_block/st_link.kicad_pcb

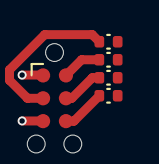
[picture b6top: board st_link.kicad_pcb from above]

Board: 4 copper layers, 5 parts (0 on the bottom side), 4 nets.

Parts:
J101: STLINK; Tag-Connect_TC2030-IDC-NL_2x03_P1.27mm_Vertical
R101, R102, R103, R104: 33; Nondescript_R_0402_1005Metric

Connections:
unnamed: J101.3 (T_NRST), R102.2
unnamed: J101.4 (T_SWCLK), R103.2
unnamed: J101.2 (T_SWDIO), R101.2
unnamed: J101.6 (T_SWO), R104.2

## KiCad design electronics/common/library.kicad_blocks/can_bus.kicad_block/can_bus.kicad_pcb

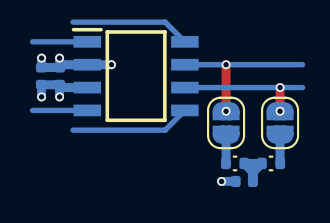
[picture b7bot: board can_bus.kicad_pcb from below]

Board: 4 copper layers, 8 parts (8 on the bottom side), 7 nets.

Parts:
C701: 1u; Nondescript_C_0402_1005Metric
C702, C703: 100n; Nondescript_C_0402_1005Metric
JP701, JP702: SolderJumper_2_Open; SolderJumper-2_P1.3mm_Open_RoundedPad1.0x1.5mm
R701, R702: 60; Nondescript_R_0402_1005Metric
U701: TCAN330DR; SOIC127P600X175-8N

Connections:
/can_bus/3V3: C701.1, C702.1, U701.3 (VCC)
/can_bus/CANH: JP701.1 (A), U701.7 (CANH)
/can_bus/CANH_TERMINATION: JP701.2 (B), R701.1
/can_bus/CANL: JP702.2 (B), U701.6 (CANL)
/can_bus/CANL_TERMINATION: JP702.1 (A), R702.2
GND: C701.2, C702.2, C703.1, U701.2 (GND)
unnamed: C703.2, R701.2, R702.1

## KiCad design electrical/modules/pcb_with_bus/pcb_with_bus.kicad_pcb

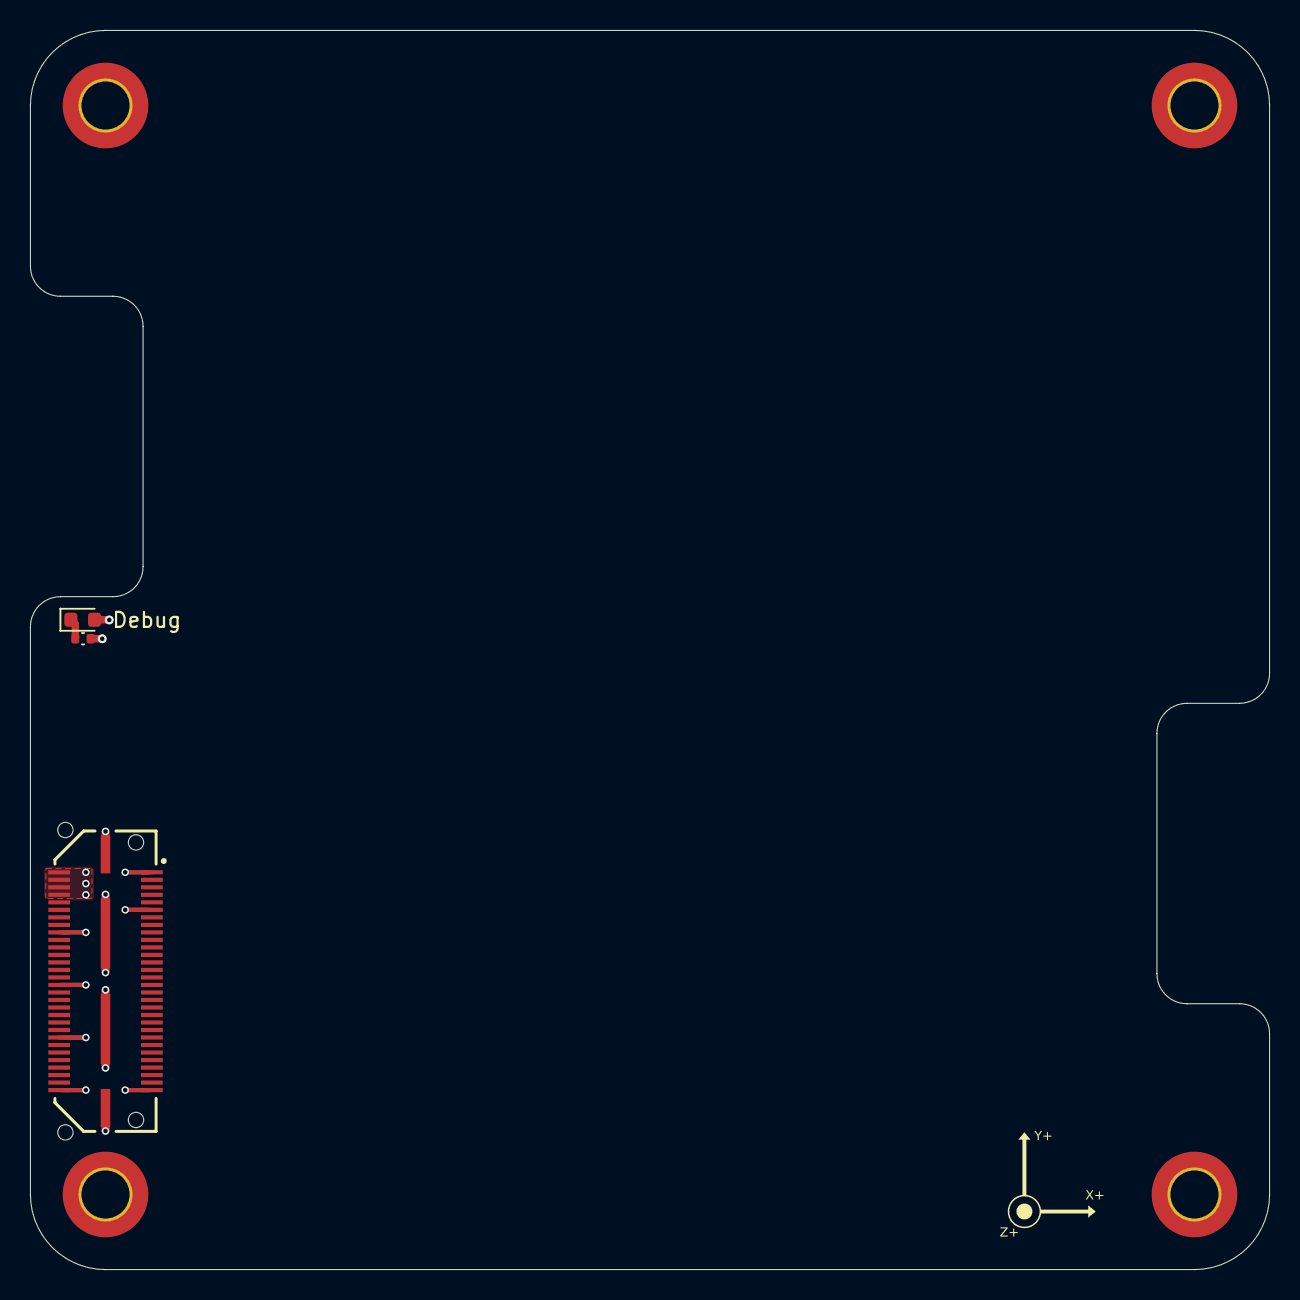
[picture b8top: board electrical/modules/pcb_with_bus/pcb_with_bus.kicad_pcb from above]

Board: 4 copper layers, 82.5 x 82.5 mm, 5 parts (1 on the bottom side), 4 nets.

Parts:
D201: Debug; LED_0603_1608Metric
J201: QTH-030-07-L-D-A; SAMTEC_QTH-030-07-L-D-A
J202: QSH-030-01-L-D-A; SAMTEC_QSH-030-01-L-D-A
PCB201: Core_Board
R201: 33; Nondescript_R_0402_1005Metric

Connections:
/VBUS: J201.01, J201.18, J201.32, J201.46, J201.60, J202.01, J202.18, J202.32, J202.46, J202.60
/VSOLAR: J201.02, J201.04, J201.06, J201.08, J202.02, J202.04, J202.06, J202.08
GND: J201.11, J201.59, J201.G1 (GND), J201.G2 (GND__1), J201.G3 (GND__2), J201.G4 (GND__3), J202.11, J202.59, J202.S1 (GND), J202.S2 (GND__1), J202.S3 (GND__2), J202.S4 (GND__3), PCB201.MH1, PCB201.MH2, PCB201.MH3, PCB201.MH4, R201.2
unnamed: D201.1 (K), R201.1
